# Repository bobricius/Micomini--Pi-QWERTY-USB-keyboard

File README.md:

# Micomini (Pi)QWERTY USB keyboard

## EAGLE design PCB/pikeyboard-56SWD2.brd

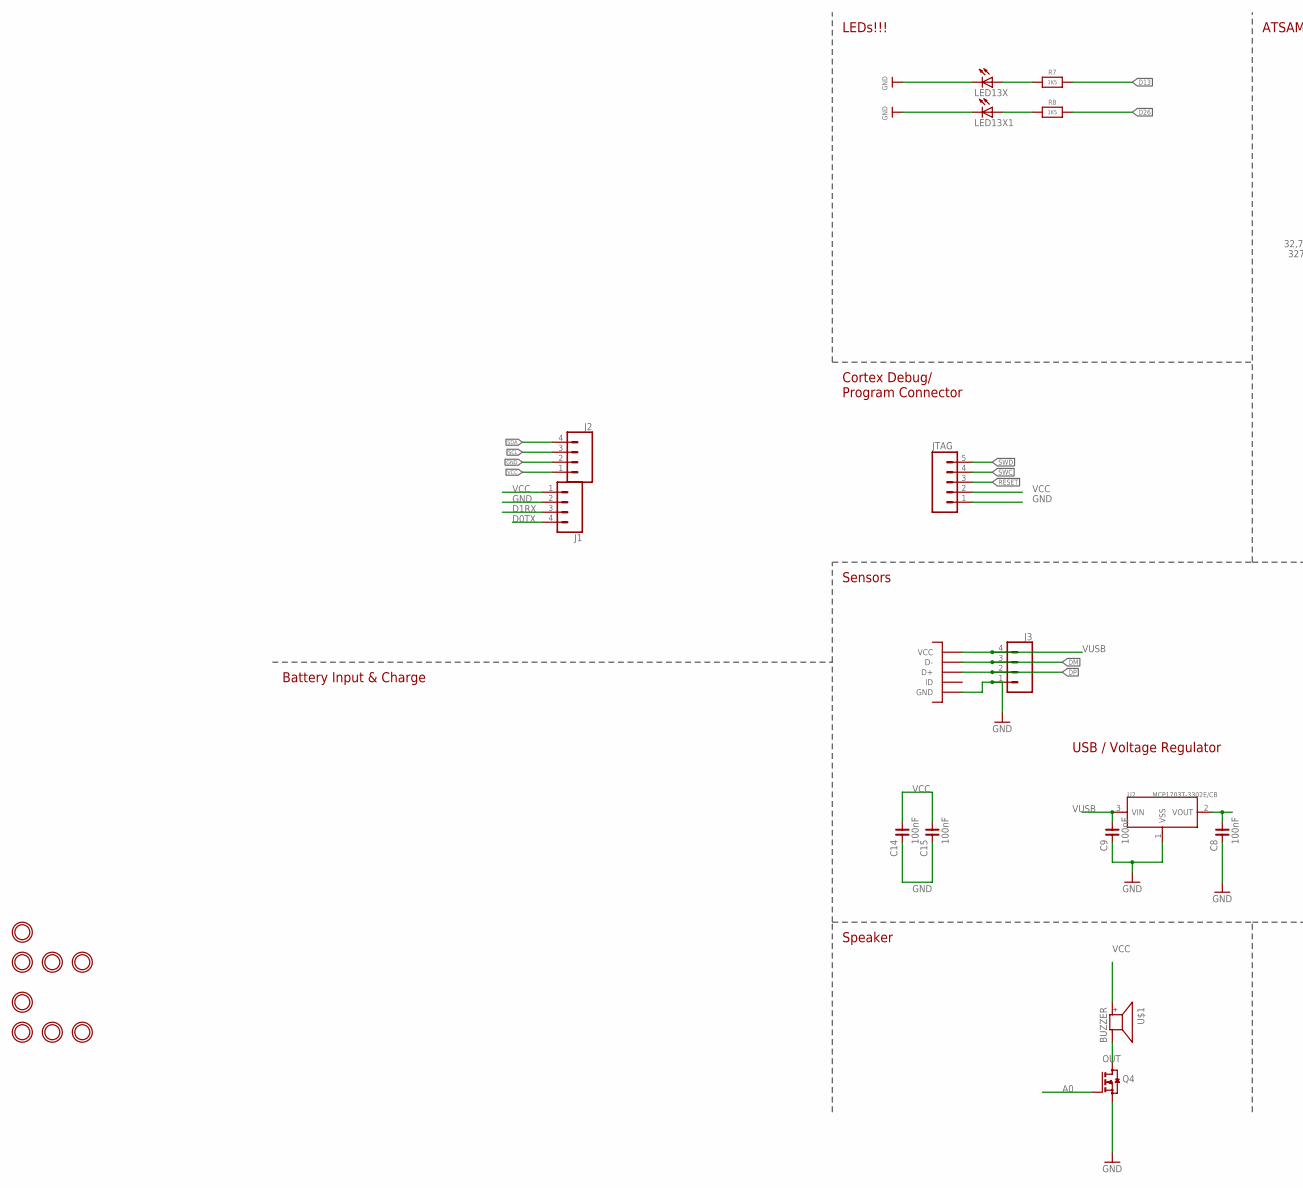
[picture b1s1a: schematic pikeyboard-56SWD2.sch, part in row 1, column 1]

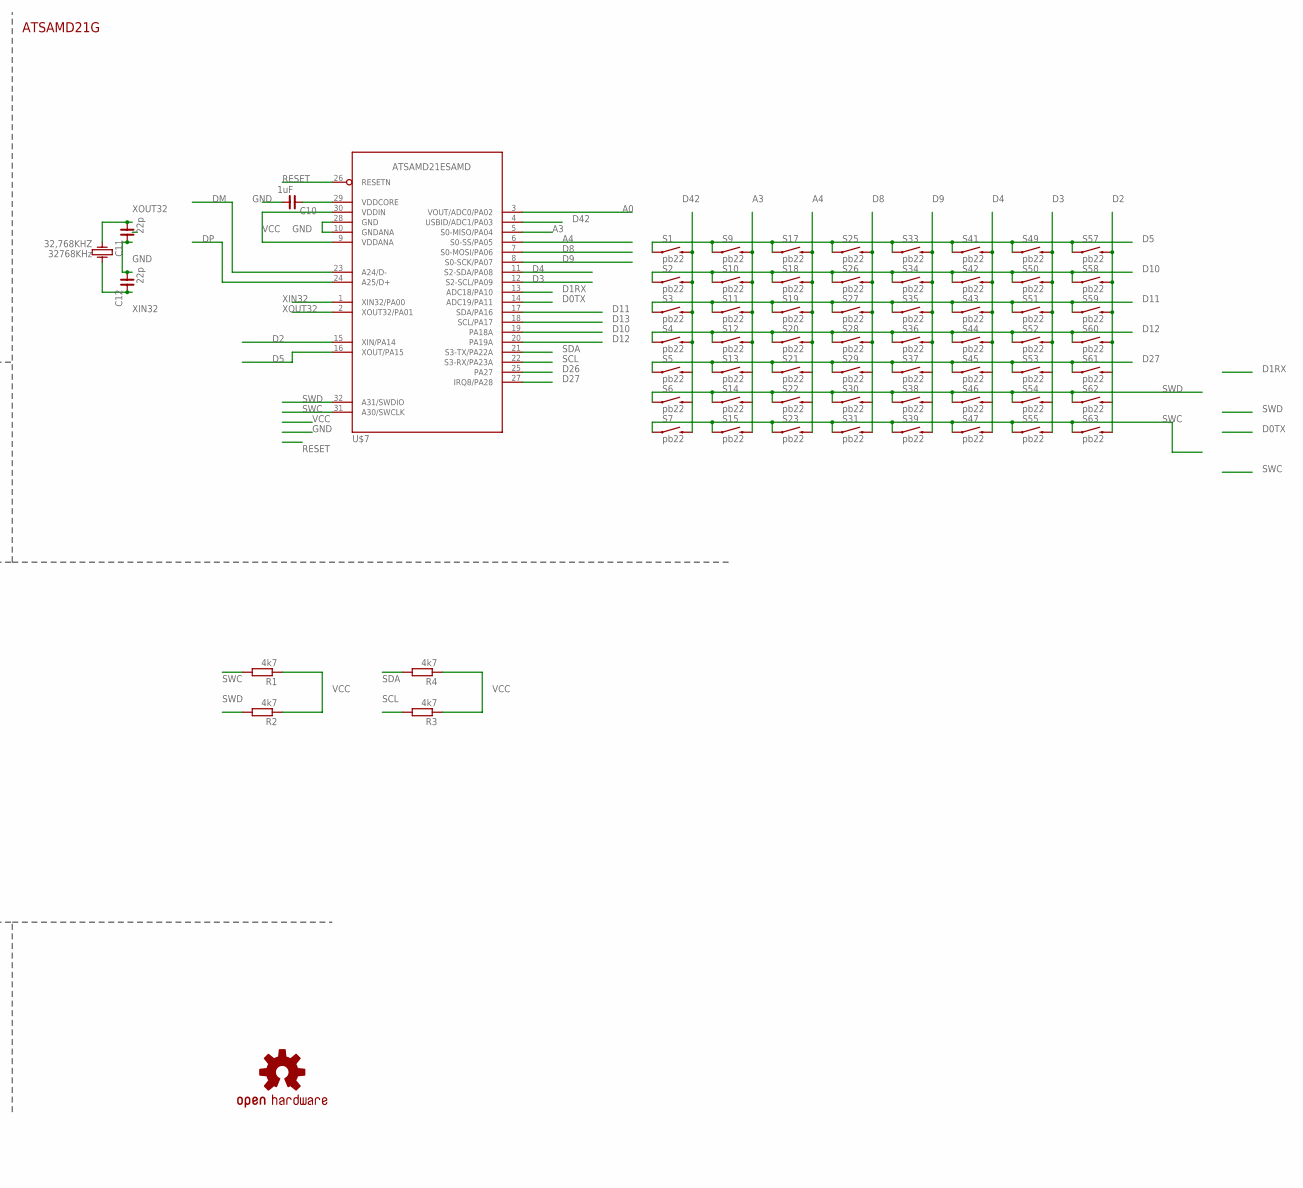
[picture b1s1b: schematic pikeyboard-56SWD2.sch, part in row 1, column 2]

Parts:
32,768KHZ: 32768KHz; KX-327LT
C8, C9, C14, C15: 100nF; C0603
C10: 1uF; C0603
C11, C12: 22p; C0603
J1, J2: CONN_041X04_NO_SILK; 1X04_NO_SILK
J3: CONN_041.27MM; 1X04_1.27MM
JTAG: M051.27MM; 1X05-1.27MM
LED13X, LED13X1: LED3MM
LOGO3: OSHW-LOGOS; OSHW-LOGO-S
Q4: BSS123; SOT23
R1, R2, R3, R4: 4k7; R0603
R7, R8: 1K5; 0603-NO
S1, S2, S3, S4, S5, S6, S7, S9, S10, S11, S12, S13, S14, S15, S17, S18, S19, S20, S21, S22, S23, S25, S26, S27, S28, S29, S30, S31, S33, S34, S35, S36, S37, S38, S39, S41, S42, S43, S44, S45, S46, S47, S49, S50, S51, S52, S53, S54, S55, S57, S58, S59, S60, S61, S62, S63: pb22; TACTILE-PTH
U2: MCP1703T-3302E/CB; SOT23
U$1: BUZZER; SMT-8585-BUZZER
U$2, U$3, U$4, U$8, U$10, U$11, U$12, U$13: MOUNTINGHOLE2.0; MOUNTINGHOLE_2.0_PLATED
U$5: MICROUSB; MICRO_B
U$7: ATSAMD21ESAMD; TQFP32-08

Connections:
A0: Q4.1 (G), U$7.3 (VOUT/ADC0/PA02)
A3: S9.3 (2), S10.3 (2), S11.3 (2), S12.3 (2), S13.3 (2), S14.3 (2), S15.3 (2), U$7.5 (S0-MISO/PA04)
A4: S17.3 (2), S18.3 (2), S19.3 (2), S20.3 (2), S21.3 (2), S22.3 (2), S23.3 (2), U$7.6 (S0-SS/PA05)
D0TX: J1.4, U$7.14 (ADC19/PA11)
D1RX: J1.3, U$7.13 (ADC18/PA10)
D2: S57.3 (2), S58.3 (2), S59.3 (2), S60.3 (2), S61.3 (2), S62.3 (2), S63.3 (2), U$7.15 (XIN/PA14)
D3: S49.3 (2), S50.3 (2), S51.3 (2), S52.3 (2), S53.3 (2), S54.3 (2), S55.3 (2), U$7.12 (S2-SCL/PA09)
D4: S41.3 (2), S42.3 (2), S43.3 (2), S44.3 (2), S45.3 (2), S46.3 (2), S47.3 (2), U$7.11 (S2-SDA/PA08)
D5: S1.1, S9.1, S17.1, S25.1, S33.1, S41.1, S49.1, S57.1, U$7.16 (XOUT/PA15)
D8: S25.3 (2), S26.3 (2), S27.3 (2), S28.3 (2), S29.3 (2), S30.3 (2), S31.3 (2), U$7.7 (S0-MOSI/PA06)
D9: S33.3 (2), S34.3 (2), S35.3 (2), S36.3 (2), S37.3 (2), S38.3 (2), S39.3 (2), U$7.8 (S0-SCK/PA07)
D10: S2.1, S10.1, S18.1, S26.1, S34.1, S42.1, S50.1, S58.1, U$7.19 (PA18A)
D11: S3.1, S11.1, S19.1, S27.1, S35.1, S43.1, S51.1, S59.1, U$7.17 (SDA/PA16)
D12: S4.1, S12.1, S20.1, S28.1, S36.1, S44.1, S52.1, S60.1, U$7.20 (PA19A)
D13: R7.1, U$7.18 (SCL/PA17)
D26: R8.1, U$7.25 (PA27)
D27: S5.1, S13.1, S21.1, S29.1, S37.1, S45.1, S53.1, S61.1, U$7.27 (IRQ8/PA28)
D42: S1.3 (2), S2.3 (2), S3.3 (2), S4.3 (2), S5.3 (2), S6.3 (2), S7.3 (2), U$7.4 (USBID/ADC1/PA03)
DM: J3.3, U$5.P2 (D-), U$7.23 (A24/D-)
DP: J3.2, U$5.P3 (D+), U$7.24 (A25/D+)
GND: C8.2, C9.2, C10.1, C11.2, C12.1, C14.2, C15.2, J1.2, J2.2, J3.1, JTAG.1, LED13X.K (C), LED13X1.K (C), Q4.2 (S), U2.1 (VSS), U$5.GND1 (GND), U$5.GND2 (GND), U$5.GND3 (GND), U$5.GND4 (GND), U$5.GND7 (GND), U$5.GND8 (GND), U$5.P5 (GND), U$7.10 (GNDANA), U$7.28 (GND)
unnamed: LED13X1.A, R8.2
unnamed: C10.2, U$7.29 (VDDCORE)
unnamed: LED13X.A, R7.2
OUT: Q4.3 (D), U$1.-
RESET: JTAG.3, U$7.26 (RESETN)
SCL: J2.3, R3.2, U$7.22 (S3-RX/PA23A)
SDA: J2.4, R4.2, U$7.21 (S3-TX/PA22A)
SWC: JTAG.4, R1.2, S7.1, S15.1, S23.1, S31.1, S39.1, S47.1, S55.1, S63.1, U$7.31 (A30/SWCLK)
SWD: JTAG.5, R2.2, S6.1, S14.1, S22.1, S30.1, S38.1, S46.1, S54.1, S62.1, U$7.32 (A31/SWDIO)
VCC: C8.1, C14.1, C15.1, J1.1, J2.1, JTAG.2, R1.1, R2.1, R3.1, R4.1, U2.2 (VOUT), U$1.+, U$7.9 (VDDANA), U$7.30 (VDDIN)
VUSB: C9.1, J3.4, U2.3 (VIN), U$5.P1 (VCC)
XIN32: 32,768KHZ.1, C12.2, U$7.1 (XIN32/PA00)
XOUT32: 32,768KHZ.4, C11.1, U$7.2 (XOUT32/PA01)

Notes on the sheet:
USB / Voltage Regulator
LEDs!!!
Cortex Debug/ Program Connector
Sensors
ATSAMD21G
Battery Input & Charge
Speaker

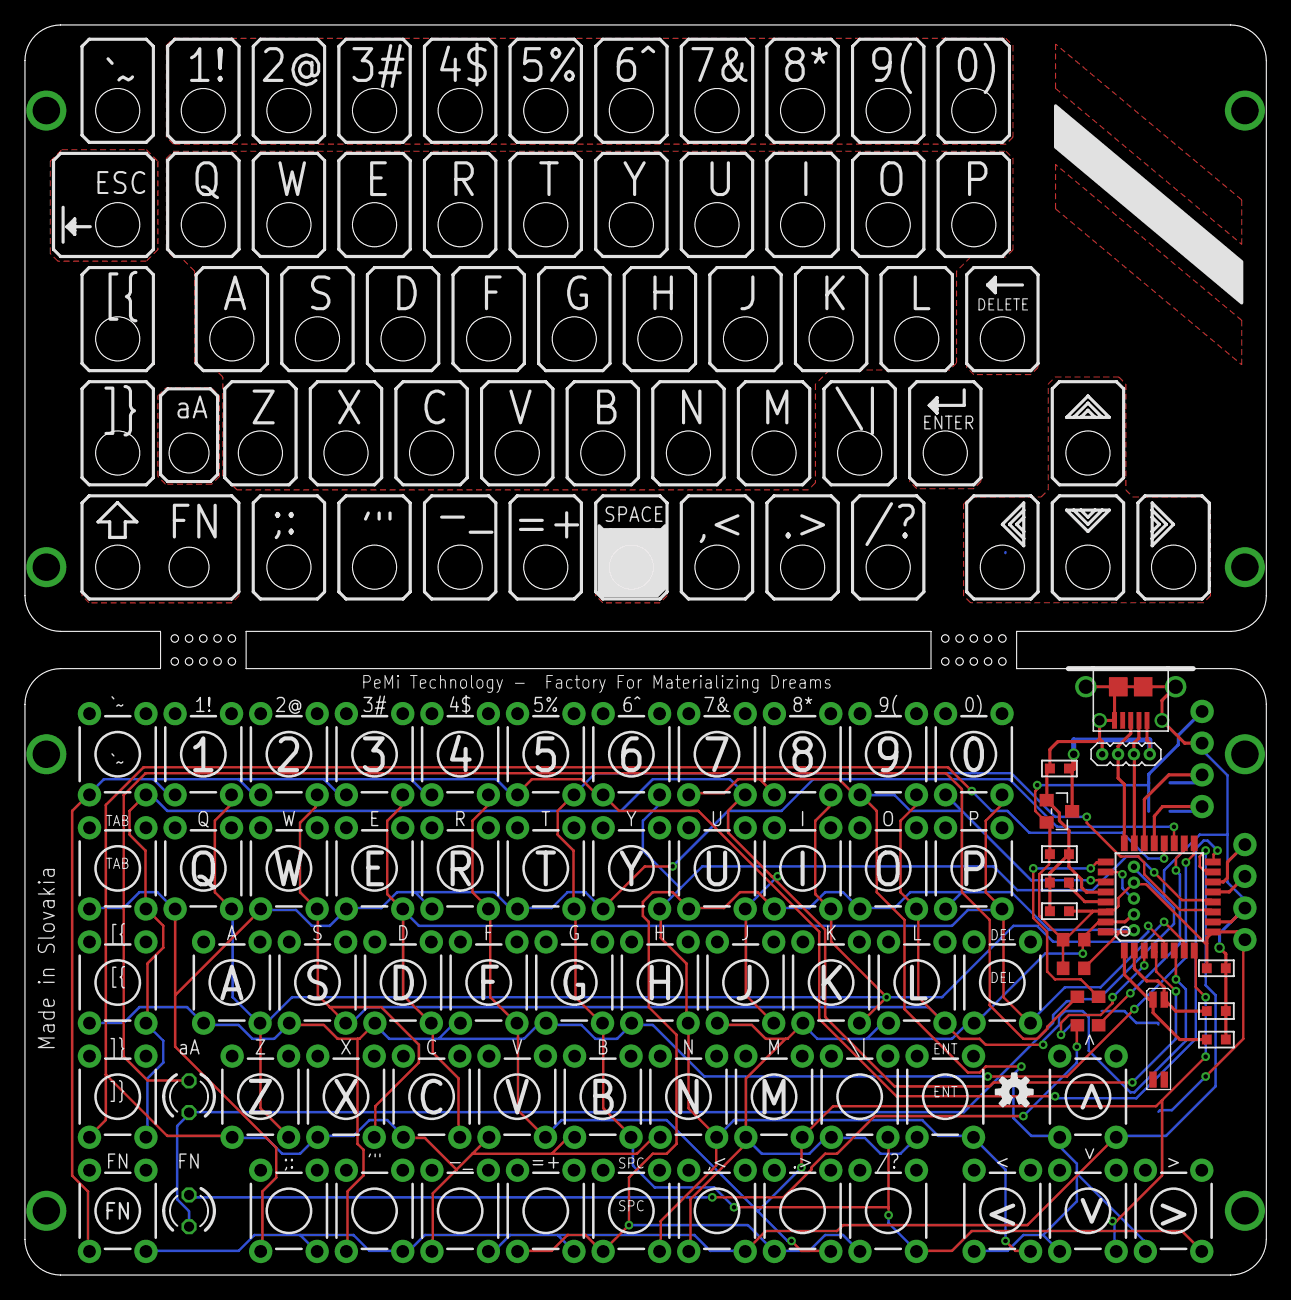
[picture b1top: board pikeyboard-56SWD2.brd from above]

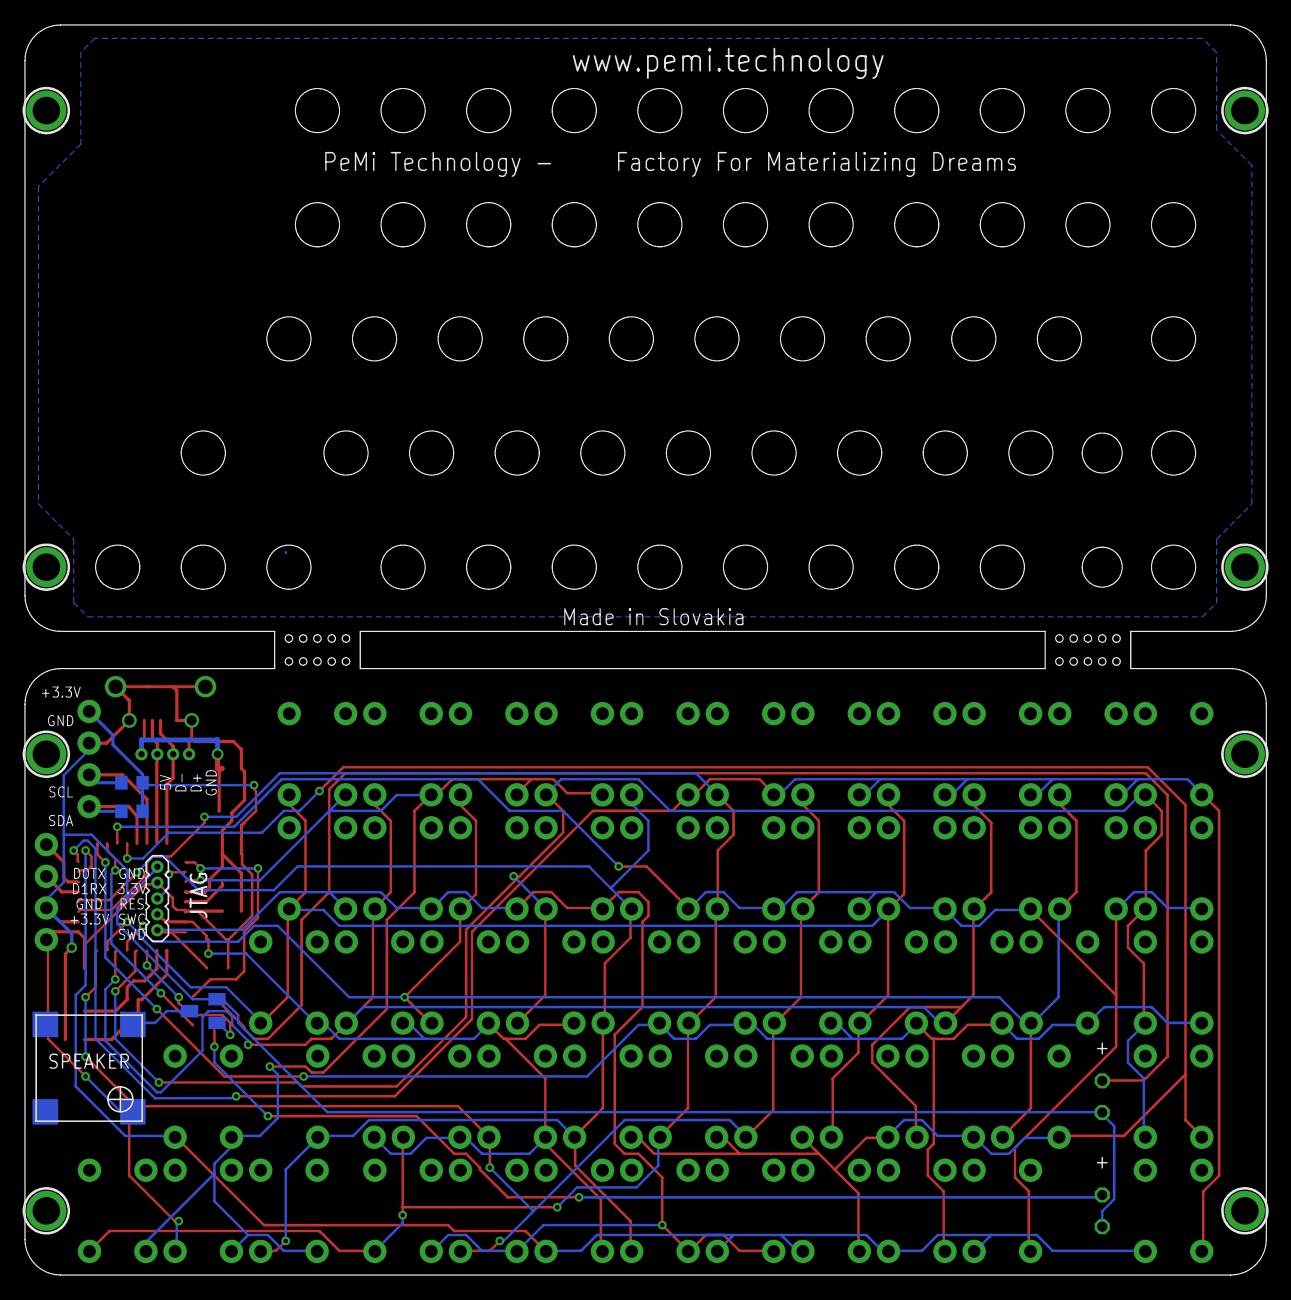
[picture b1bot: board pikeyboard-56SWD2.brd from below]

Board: 2 copper layers, 99.4 x 100.1 mm, 90 parts (13 on the bottom side), 34 nets.

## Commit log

2018-08-11 init
    First upload
2021-03-03 Add files via upload
    Schematic in png format

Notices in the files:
parts and their libraries:
SparkFun-Aesthetics: Licensing: Creative Commons ShareAlike 4.0 International - https://creativecommons.org/licenses/by-sa/4.0
